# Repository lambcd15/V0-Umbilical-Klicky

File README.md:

# V0-Umbilical-Klicky
Voron V0 / V0.1 Umbilical remix for klicky probe

This is remix of timmit99 Umbilical cable mod for the Voron V0.1, I have chanegd the design to add in the z-end stop of klicky probe function as I want a clean look, I may later add the I2C wiring for the ADXL345 for input shaping.

The bill of materials is the same as timmit99 but with a 16 pin Molex not a 14 pin.

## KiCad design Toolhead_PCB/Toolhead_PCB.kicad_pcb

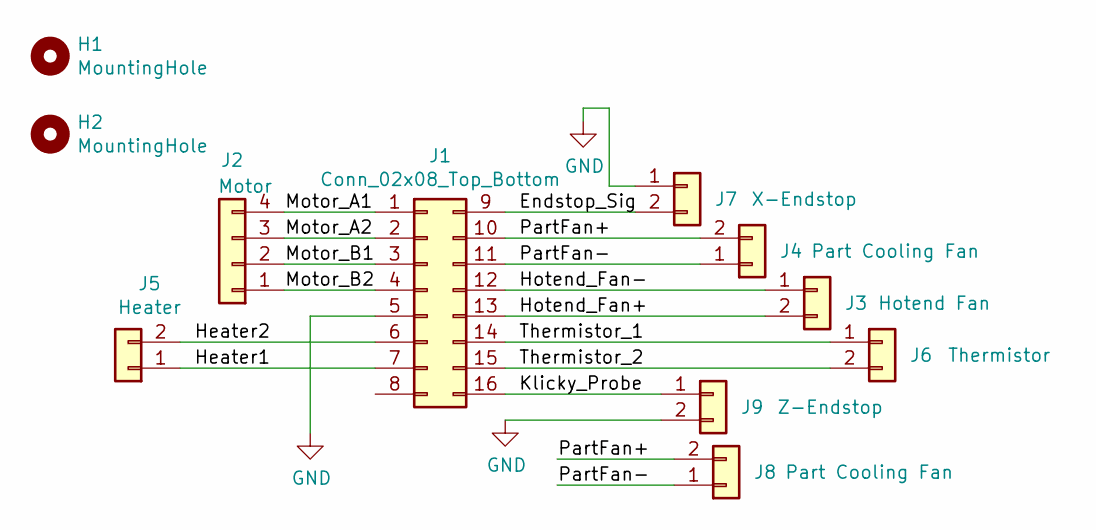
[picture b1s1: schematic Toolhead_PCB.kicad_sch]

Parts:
H1, H2: MountingHole; MountingHole_3.2mm_M3
J1: Conn_02x08_Top_Bottom; Molex_Micro-Fit_3.0_43045-1600_2x08_P3.00mm_Horizontal
J2: Motor; JST_XH_B4B-XH-A_1x04_P2.50mm_Vertical
J3: Hotend Fan; JST_XH_B2B-XH-A_1x02_P2.50mm_Vertical
J4, J8: Part Cooling Fan; JST_XH_B2B-XH-A_1x02_P2.50mm_Vertical
J5: Heater; JST_XH_B2B-XH-A_1x02_P2.50mm_Vertical
J6: Thermistor; JST_XH_B2B-XH-A_1x02_P2.50mm_Vertical
J7: X-Endstop; JST_XH_B2B-XH-A_1x02_P2.50mm_Vertical
J9: Z-Endstop; JST_XH_B2B-XH-A_1x02_P2.50mm_Vertical

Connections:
/Endstop_Sig: J1.9, J7.2
/Heater1: J1.7, J5.1
/Heater2: J1.6, J5.2
/Hotend_Fan+: J1.13, J3.2
/Hotend_Fan-: J1.12, J3.1
/Klicky_Probe: J1.16, J9.1
/Motor_A1: J1.1, J2.4
/Motor_A2: J1.2, J2.3
/Motor_B1: J1.3, J2.2
/Motor_B2: J1.4, J2.1
/PartFan+: J1.10, J4.2, J8.2
/PartFan-: J1.11, J4.1, J8.1
/Thermistor_1: J1.14, J6.1
/Thermistor_2: J1.15, J6.2
GND: J1.5, J7.1, J9.2

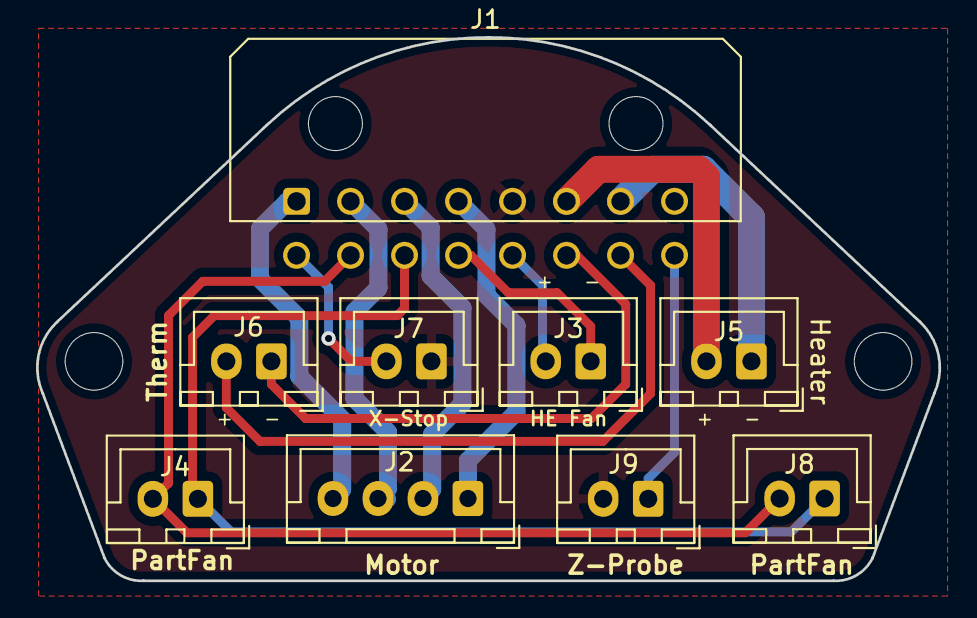
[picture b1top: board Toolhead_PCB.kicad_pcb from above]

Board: 2 copper layers, 50.1 x 30.2 mm, 11 parts (0 on the bottom side), 15 nets.

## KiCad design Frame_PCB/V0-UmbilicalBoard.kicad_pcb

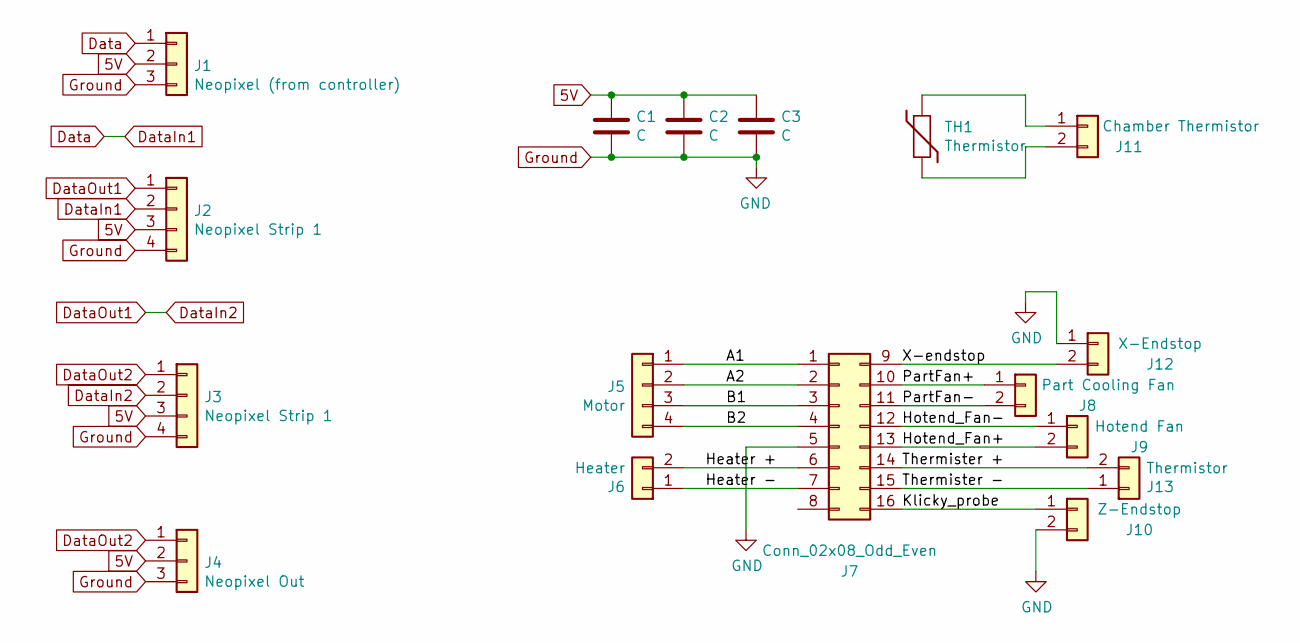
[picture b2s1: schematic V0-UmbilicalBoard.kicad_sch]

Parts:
C1, C2, C3: C; C_0805_2012Metric_Pad1.18x1.45mm_HandSolder
J1: Neopixel (from controller); JST_XH_B3B-XH-A_1x03_P2.50mm_Vertical
J2, J3: Neopixel Strip 1; JST_XH_B4B-XH-A_1x04_P2.50mm_Vertical
J4: Neopixel Out; JST_XH_B3B-XH-A_1x03_P2.50mm_Vertical
J5: Motor; JST_XH_B4B-XH-A_1x04_P2.50mm_Vertical
J6: Heater; TerminalBlock_Phoenix_MKDS-1,5-2-5.08_1x02_P5.08mm_Horizont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
J7: Conn_02x08_Odd_Even; Molex_Micro-Fit_3.0_43045-1612_2x08_P3.00mm_Vertical
J8: Part Cooling Fan; JST_XH_B2B-XH-A_1x02_P2.50mm_Vertical
J9: Hotend Fan; JST_XH_B2B-XH-A_1x02_P2.50mm_Vertical
J10: Z-Endstop; JST_XH_B2B-XH-A_1x02_P2.50mm_Vertical
J11: Chamber Thermistor; JST_XH_B2B-XH-A_1x02_P2.50mm_Vertical
J12: X-Endstop; JST_XH_B2B-XH-A_1x02_P2.50mm_Vertical
J13: Thermistor; JST_XH_B2B-XH-A_1x02_P2.50mm_Vertical
TH1: Thermistor; R_0805_2012Metric_Pad1.20x1.40mm_HandSolder

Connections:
5V: C1.1, C2.1, C3.1, J1.2, J2.3, J3.3, J4.2
/A1: J5.1, J7.1
/A2: J5.2, J7.2
/B1: J5.3, J7.3
/B2: J5.4, J7.4
/Heater +: J6.2, J7.6
/Heater -: J6.1, J7.7
/Hotend_Fan+: J7.13, J9.2
/Hotend_Fan-: J7.12, J9.1
/Klicky_probe: J7.16, J10.1
/PartFan+: J7.10, J8.1
/PartFan-: J7.11, J8.2
/Thermister +: J7.14, J13.2
/Thermister -: J7.15, J13.1
/X-endstop: J7.9, J12.2
Data: J1.1, J2.2
DataIn2: J2.1, J3.2
DataOut2: J3.1, J4.1
Ground: C1.2, C2.2, C3.2, J1.3, J2.4, J3.4, J4.3, J7.5, J10.2, J12.1
unnamed: J11.1, TH1.1
unnamed: J11.2, TH1.2

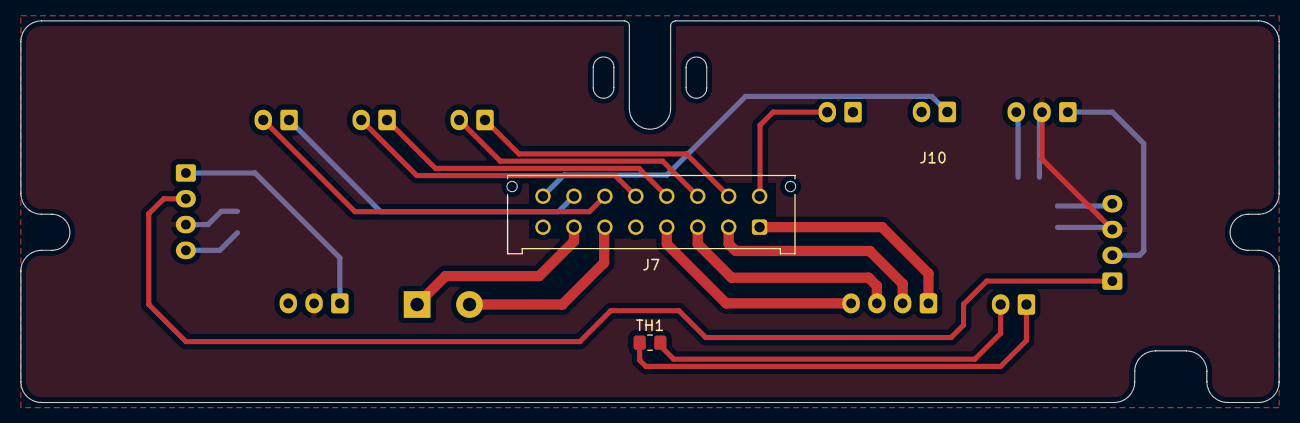
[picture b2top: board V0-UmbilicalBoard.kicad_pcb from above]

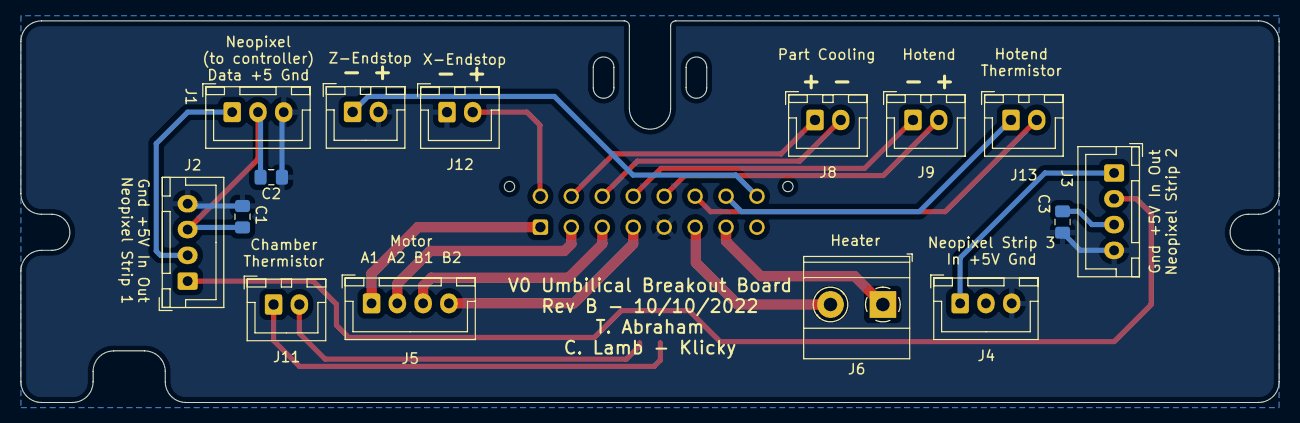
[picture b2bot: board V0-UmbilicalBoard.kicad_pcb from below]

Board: 2 copper layers, 122.0 x 37.0 mm, 17 parts (15 on the bottom side), 21 nets.

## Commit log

2022-10-10 Kicad Project Files
